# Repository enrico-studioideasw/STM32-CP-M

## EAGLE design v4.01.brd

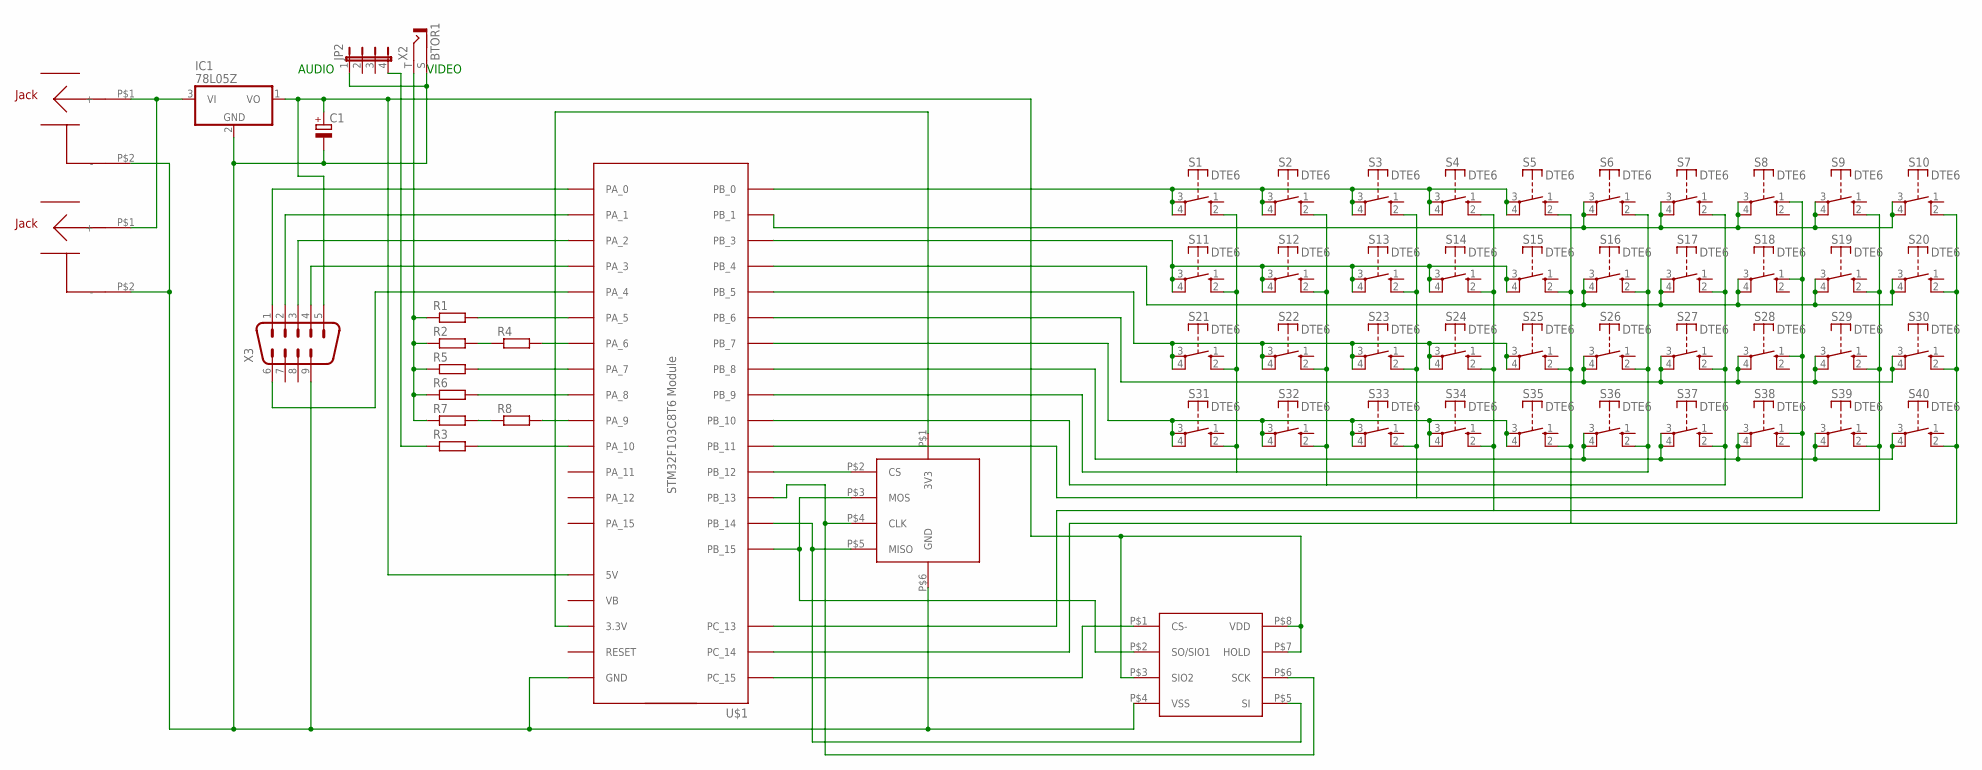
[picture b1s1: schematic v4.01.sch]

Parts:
C1: CPOL-EUE3.5-8; E3,5-8
IC1: 78L05Z; TO92
JP2: JP4E; JP4
R1, R2, R3, R4, R5, R6, R7, R8: R-EU_0204/2V; 0204V
S1, S2, S3, S4, S5, S6, S7, S8, S9, S10, S11, S12, S13, S14, S15, S16, S17, S18, S19, S20, S21, S22, S23, S24, S25, S26, S27, S28, S29, S30, S31, S32, S33, S34, S35, S36, S37, S38, S39, S40: DTE6
U$1: STM32F103C8T6-MODULE
U$2: SD-READER; SD_READER
U$3: 23LC1024; 4DIP
U$4, U$5: JACK-PLUG
X2: BTOR1
X3: M09D

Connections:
unnamed: C1.+, IC1.1 (VO), U$1.5V, U$3.P$3 (SIO2), U$3.P$7 (HOLD), U$3.P$8 (VDD), X3.5
unnamed: U$1.PA_0, X3.1
unnamed: U$1.PA_1, X3.2
unnamed: U$1.PA_2, X3.3
unnamed: U$1.PA_3, X3.4
unnamed: U$1.PA_4, X3.6
unnamed: R1.1, R2.1, R5.1, R6.1, R7.1, X2.T (1)
unnamed: R1.2, U$1.PA_5
unnamed: R2.2, R4.1
unnamed: JP2.4, R3.1
unnamed: R4.2, U$1.PA_6
unnamed: U$1.3.3V@1 (3.3V), U$1.3.3V@2 (3.3V), U$2.P$1 (3V3)
unnamed: C1.-, IC1.2 (GND), JP2.1, U$1.GND@1 (GND), U$1.GND@2 (GND), U$1.GND@3 (GND), U$2.P$6 (GND), U$3.P$4 (VSS), U$4.P$2 (-), U$5.P$2 (-), X2.S (2), X3.9
unnamed: U$1.PB_15, U$2.P$3 (MOS), U$3.P$2 (SO/SIO1)
unnamed: U$1.PB_14, U$2.P$5 (MISO), U$3.P$5 (SI)
unnamed: U$1.PB_13, U$2.P$4 (CLK), U$3.P$6 (SCK)
unnamed: U$1.PB_12, U$2.P$2 (CS)
unnamed: S1.3, S1.4, S2.3, S2.4, S3.3, S3.4, S4.3, S4.4, S5.3, S5.4, U$1.PB_0
unnamed: S6.3, S6.4, S7.3, S7.4, S8.3, S8.4, S9.3, S9.4, S10.3, S10.4, U$1.PB_1
unnamed: S11.3, S11.4, S12.3, S12.4, S13.3, S13.4, S14.3, S14.4, S15.3, S15.4, U$1.PB_3
unnamed: S16.3, S16.4, S17.3, S17.4, S18.3, S18.4, S19.3, S19.4, S20.3, S20.4, U$1.PB_4
unnamed: S21.3, S21.4, S22.3, S22.4, S23.3, S23.4, S24.3, S24.4, S25.3, S25.4, U$1.PB_5
unnamed: S26.3, S26.4, S27.3, S27.4, S28.3, S28.4, S29.3, S29.4, S30.3, S30.4, U$1.PB_6
unnamed: S31.3, S31.4, S32.3, S32.4, S33.3, S33.4, S34.3, S34.4, S35.3, S35.4, U$1.PB_7
unnamed: S36.3, S36.4, S37.3, S37.4, S38.3, S38.4, S39.3, S39.4, S40.3, S40.4, U$1.PB_8
unnamed: S1.2 (S), S6.2 (S), S11.2 (S), S16.2 (S), S21.2 (S), S26.2 (S), S31.2 (S), S36.2 (S), U$1.PB_9
unnamed: S2.2 (S), S7.2 (S), S12.2 (S), S17.2 (S), S22.2 (S), S27.2 (S), S32.2 (S), S37.2 (S), U$1.PB_10
unnamed: S3.2 (S), S8.1 (S), S13.2 (S), S18.1 (S), S23.2 (S), S28.1 (S), S33.2 (S), S38.1 (S), U$1.PB_11
unnamed: S4.2 (S), S9.2 (S), S14.2 (S), S19.2 (S), S24.2 (S), S29.2 (S), S34.2 (S), S39.2 (S), U$1.PC_13
unnamed: S5.2 (S), S10.2 (S), S15.2 (S), S20.2 (S), S25.2 (S), S30.2 (S), S35.2 (S), S40.2 (S), U$1.PC_14
unnamed: U$1.PC_15, U$3.P$1 (CS-)
unnamed: IC1.3 (VI), U$4.P$1 (+), U$5.P$1 (+)
unnamed: R7.2, R8.1
unnamed: R8.2, U$1.PA_9
unnamed: R6.2, U$1.PA_8
unnamed: R5.2, U$1.PA_7
unnamed: R3.2, U$1.PA_10

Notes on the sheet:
VIDEO
AUDIO

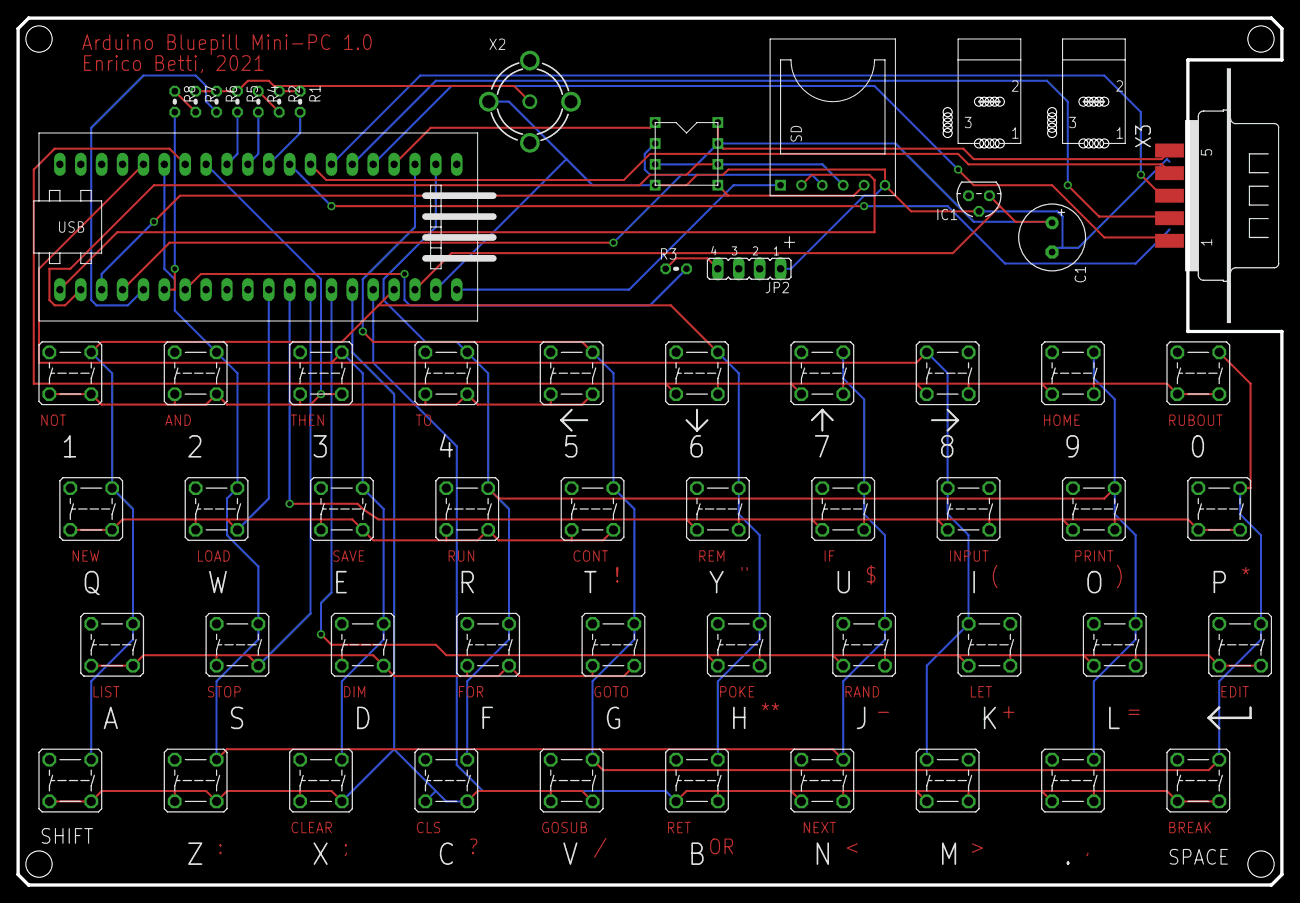
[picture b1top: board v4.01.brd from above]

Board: 2 copper layers, 153.7 x 105.4 mm, 58 parts (0 on the bottom side), 37 nets.

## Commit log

2026-06-17 Add files via upload
    schema elettrico e board di eagle, richiede qualche piccolo patch.
